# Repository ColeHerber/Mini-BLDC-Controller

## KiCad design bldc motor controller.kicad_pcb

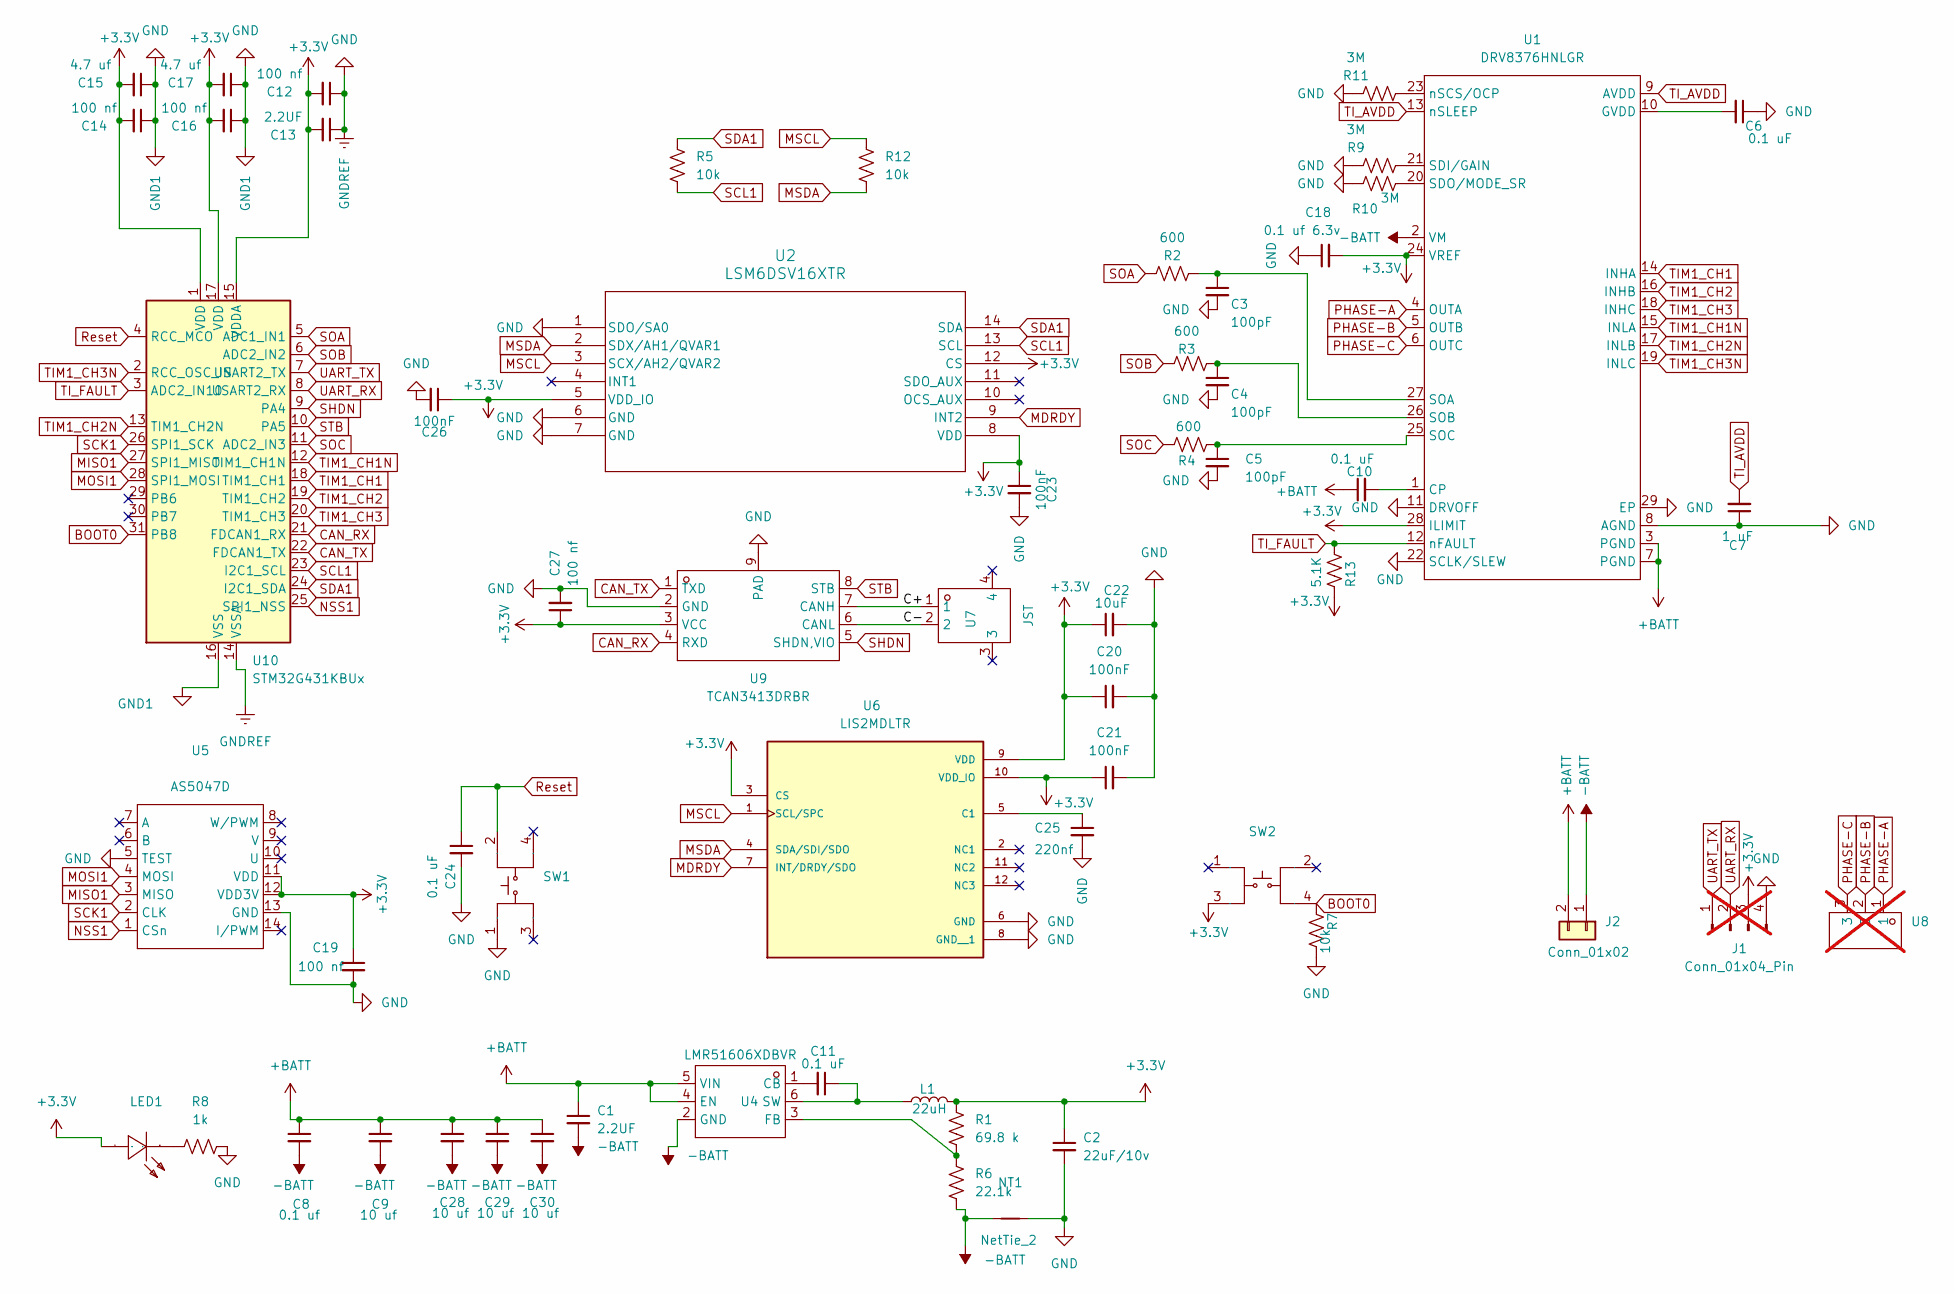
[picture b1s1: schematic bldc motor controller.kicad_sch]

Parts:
C1: 2.2UF; C_1206_3216Metric
C2: 22uF/10v; C_0805_2012Metric
C3, C4, C5: 100pF; C_0201_0603Metric
C6: 0.1 uF; C_01005_0402Metric
C7: 1 uF; C_0603_1608Metric
C8: 0.1 uf; C_0402_1005Metric
C9, C28, C29, C30: 10 uf; C_0603_1608Metric
C10, C11, C24: 0.1 uF; C_0402_1005Metric
C12, C14, C16, C19, C27: 100 nf; C_0201_0603Metric
C13: 2.2UF; C_0603_1608Metric
C15, C17: 4.7 uf; C_0603_1608Metric
C18: 0.1 uf 6.3v; C_0402_1005Metric
C20, C21, C23, C26: 100nF; C_0201_0603Metric
C22: 10uF; C_0603_1608Metric
C25: 220nf; C_0402_1005Metric
J1: Conn_01x04_Pin; PinHeader_1x04_P1.00mm_Vertical; not fitted
J2: Conn_01x02; JST_EH_B2B-EH-A_1x02_P2.50mm_Vertical
L1: 22uH; L_Bourns_SRP5030T
LED1: LED_0603_1608Metric; Manufacturer Part KT-0603R; LCSC Part Name 0603 红灯 高亮
NT1: NetTie_2; NetTie-2_SMD_Pad0.5mm
R1: 69.8 k; C_0805_2012Metric
R2, R3, R4: 600; R_0201_0603Metric
R5, R7, R12: 10k; R_0402_1005Metric
R6: 22.1k; R_0603_1608Metric
R8: 1k; R_0603_1608Metric
R9, R10, R11: 3M; R_0402_1005Metric
R13: 5.1K; R_0603_1608Metric
SW1, SW2: KEY-SMD_4P-L2.6-W1.6-P0.80-LS3.0; Manufacturer Part SKTAACE010; LCSC Part Name 2.6*1.6*0.53mm 立贴 轻触开关
U1: VQFN-28_L6.0-W5.0-P0.50-TL-EP4.0; Manufacturer Part DRV8376HNLGR; LCSC Part Name DRV8376HNLGR
U2: LSM6DSV16XTR; LGA-14L_STM
U4: SOT-23-6_L2.9-W1.6-P0.95-LS2.8-BR; Manufacturer Part LMR51606XDBVR; LCSC Part Name 4V至65V输入电压范围的0.6A同步降压转换器
U5: TSSOP-14_L5.0-W4.4-P0.65-LS6.4-BL; Manufacturer Part AS5047D; LCSC Part Name AS5047D-ATSM
U6: LIS2MDLTR; PQFN50P200X200X70-12N; PARTREV Rev 5
U7: JST_GH_BM02B-GHS-TBT_1x02-1MP_P1.25mm_Vertical; Manufacturer Part SM02B-GHS-TB(LF)(SN); LCSC Part Name 1x2P 间距:1.25mm 卧贴 系列:GH
U8: PinHeader_1x03_P2.54mm_Vertical; Manufacturer Part MR30-M; LCSC Part Name AMASS(艾迈斯)锂电池三芯电源连接器公头MR30-M 2件套; not fitted
U9: SON-8_L3.0-W3.0-P0.65-LS2.9-BL-EP; Manufacturer Part TCAN3413DRBR; LCSC Part Name TCAN3413DRBR
U10: STM32G431KBUx; QFN-32-1EP_5x5mm_P0.5mm_EP3.45x3.45mm

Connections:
+3.3V: C2.1, C12.2, C13.2, C14.2, C15.2, C16.2, C17.2, C18.2, C19.1, C20.1, C21.1, C22.1, C23.1, C26.1, C27.1, J1.3, L1.2, LED1.2 (A), R1.1, R13.2, SW2.3, U1.24 (VREF), U1.28 (ILIMIT), U2.5 (VDD_IO), U2.8 (VDD), U2.12 (CS), U5.11 (VDD), U5.12 (VDD3V), U6.3 (CS), U6.9 (VDD), U6.10 (VDD_IO), U9.3 (VCC), U10.1 (VDD), U10.15 (VDDA), U10.17 (VDD)
+BATT: C1.1, C8.1, C9.1, C10.1, C28.1, C29.1, C30.1, J2.2, U1.3 (PGND), U1.7 (PGND), U4.4 (EN), U4.5 (VIN)
-BATT: C1.2, C8.2, C9.2, C28.2, C29.2, C30.2, J2.1, NT1.1, R6.2, U1.2 (VM), U4.2 (GND)
/C+: U7.1, U9.7 (CANH)
/C-: U7.2, U9.6 (CANL)
BOOT0: R7.1, SW2.4, U10.31 (PB8)
CAN_RX: U9.4 (RXD), U10.21 (FDCAN1_RX)
CAN_TX: U9.1 (TXD), U10.22 (FDCAN1_TX)
GND: C2.2, C3.2, C4.2, C5.2, C6.1, C7.1, C12.1, C13.1, C14.1, C15.1, C16.1, C17.1, C18.1, C19.2, C20.2, C21.2, C22.2, C23.2, C24.2, C25.2, C26.2, C27.2, J1.4, NT1.2, R7.2, R8.2, R9.2, R10.2, R11.2, SW1.1, U1.8 (AGND), U1.11 (DRVOFF), U1.22 (SCLK/SLEW), U1.29 (EP), U2.1 (SDO/SA0), U2.6 (GND), U2.7 (GND), U5.5 (TEST), U5.13 (GND), U6.6 (GND), U6.8 (GND__1), U9.2 (GND), U9.9 (PAD), U10.14 (VSSA), U10.16 (VSS), U10.32 (VSS), U10.33 (VSS)
MDRDY: U2.9 (INT2), U6.7 (INT/DRDY/SDO)
MISO1: U5.3 (MISO), U10.27 (SPI1_MISO)
MOSI1: U5.4 (MOSI), U10.28 (SPI1_MOSI)
MSCL: R12.1, U2.3 (SCX/AH2/QVAR2), U6.1 (SCL/SPC)
MSDA: R12.2, U2.2 (SDX/AH1/QVAR1), U6.4 (SDA/SDI/SDO)
NSS1: U5.1 (CSn), U10.25 (SPI1_NSS)
unnamed: LED1.1 (K), R8.1
unnamed: C10.2, U1.1 (CP)
unnamed: C6.2, U1.10 (GVDD)
unnamed: R9.1, U1.21 (SDI/GAIN)
unnamed: R10.1, U1.20 (SDO/MODE_SR)
unnamed: C3.1, R2.1, U1.27 (SOA)
unnamed: C4.1, R3.1, U1.26 (SOB)
unnamed: C5.1, R4.1, U1.25 (SOC)
unnamed: R11.1, U1.23 (nSCS/OCP)
unnamed: C11.2, U4.1 (CB)
unnamed: R1.2, R6.1, U4.3 (FB)
unnamed: C11.1, L1.1, U4.6 (SW)
unnamed: C25.1, U6.5 (C1)
PHASE-A: U1.4 (OUTA), U8.1
PHASE-B: U1.5 (OUTB), U8.2
PHASE-C: U1.6 (OUTC), U8.3
Reset: C24.1, SW1.2, U10.4 (RCC_MCO)
SCK1: U5.2 (CLK), U10.26 (SPI1_SCK)
SCL1: R5.2, U2.13 (SCL), U10.23 (I2C1_SCL)
SDA1: R5.1, U2.14 (SDA), U10.24 (I2C1_SDA)
SHDN: U9.5 (SHDN,VIO), U10.9 (PA4)
SOA: R2.2, U10.5 (ADC1_IN1)
SOB: R3.2, U10.6 (ADC2_IN2)
SOC: R4.2, U10.11 (ADC2_IN3)
STB: U9.8 (STB), U10.10 (PA5)
TIM1_CH1: U1.14 (INHA), U10.18 (TIM1_CH1)
TIM1_CH1N: U1.15 (INLA), U10.12 (TIM1_CH1N)
TIM1_CH2: U1.16 (INHB), U10.19 (TIM1_CH2)
TIM1_CH2N: U1.17 (INLB), U10.13 (TIM1_CH2N)
TIM1_CH3: U1.18 (INHC), U10.20 (TIM1_CH3)
TIM1_CH3N: U1.19 (INLC), U10.2 (RCC_OSC_IN)
TI_AVDD: C7.2, U1.9 (AVDD), U1.13 (nSLEEP)
TI_FAULT: R13.1, U1.12 (nFAULT), U10.3 (ADC2_IN10)
UART_RX: J1.2, U10.8 (LPUART1_RX)
UART_TX: J1.1, U10.7 (LPUART1_TX)

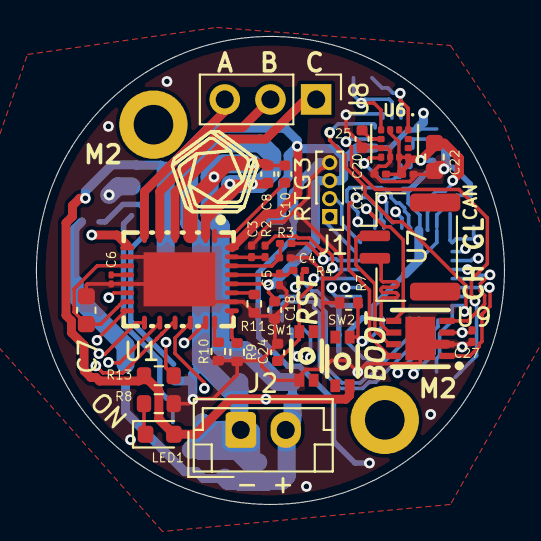
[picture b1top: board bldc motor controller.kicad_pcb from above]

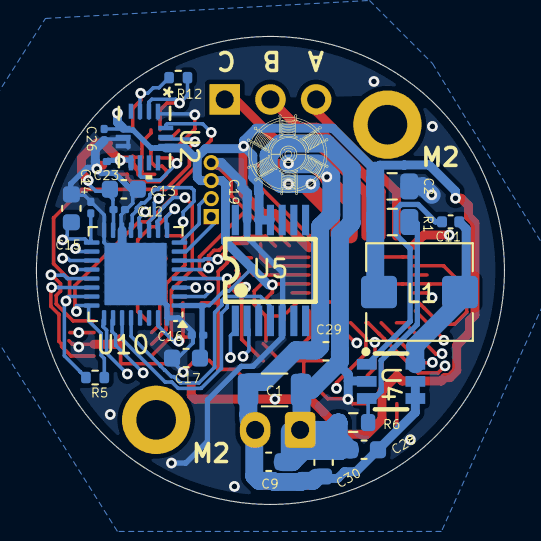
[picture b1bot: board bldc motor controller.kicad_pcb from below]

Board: 4 copper layers, 26.0 x 26.0 mm, 61 parts (26 on the bottom side), 50 nets.

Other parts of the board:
M2, M2#2: MountingHole_2.2mm_M2_DIN965_Pad

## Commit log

2025-09-29 first commit green
2025-10-01 did a lot of work, swapped out basically every chip at least once. Good times. Need to actually use global frames like EFR
2025-10-03 fuck yeah is closing in
2025-10-03 I give up it'll be a 4 layer
2025-10-05 Almost done design, need to add mounting holes I think
2025-10-05 yeee haw
2025-10-09 Power Ground Signal Ground Seperate
2025-10-14 4 layer nice looking board
2025-10-14 resistor for current sense did not exist
2025-10-14 updated certain capacitor sizes, doubled power vias for saftey
2025-10-16 Big push before imu swap
2025-10-16 Updated schematic with new imu
2025-10-16 Updated PCB, need to do some tweaks on motor controller schematic side
2025-10-16 Centered encoder sensor
2025-10-16 Final push of the day
2025-10-17 Wooo added a can transciever
2025-10-18 Going to try to fix battery routing
2025-10-18 Re-routed power
2025-10-23 updated to min capacitor size and increased width of 3.3v rail
2025-10-24 3.3v plane, finale besides that
2025-10-24 silkscreen ain't going to work but that is ok
2025-11-01 final review time
2025-11-02 and I think I am done! oh boy oh boy
